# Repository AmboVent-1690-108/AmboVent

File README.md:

# AmboVent  1690.108

[![Travis Status][S]][T]

    Automatic, Controlled Resuscitator Device
    Emergency ventilation alternative system
    Global Partnership for the Greater good
    Leading Open Source Code Mentality Initiative

## Emergency ventilation initiative coming out of Israel

## The device was not tested yet for its performance or safety; it is NOT approved for clinical use

### Who is behind it?  
**Lead by the CTO & innovation leader of the Israeli Air-Force 108 Electronic Depot and backed by a large community of innovators behind him, to include:**

1. 40 Professional Volunteers
1. Magen David Adom (Israel’s national EMS)
1. Physicians from leading Israeli hospitals such as Tel Aviv Sourasky and Hadassah JLM as well as other medical centers, Engineers, FIRST Israel mentors and students
1. The Haifa Technological Center Rafael
1. Israel Aerospace Industries
1. IAF Unit 108
1. The garage program by Microsoft Israel
1. IDC Herzeliya
1. and others...

## Developer Chat on Gitter:

## [AmboVent Website](https://1nn0v8ter.rocks/AmboVent-1690-108)

## [BOM list](https://docs.google.com/spreadsheets/d/1yqxRhruZpR-hO4cpbX6UkSeXTlXk1JLd_4aYDwuWj4k/edit?usp=sharing)

# AmboVent's Standard Copyright and Disclaimer Notice:

*Copyright ©2020. THE AMBOVENT GROUP FROM ISRAEL herby declares:  No Rights Reserved. Anyone in the world have Permission to use, copy, modify, and distribute this software and its documentation for educational, research, for profit, business and not-for-profit purposes, without fee and without a signed licensing agreement, all is hereby granted, provided that the intention of the user is to use this code and documentation to save human lives  anywhere in the world. For any question, contact dreliram@gmail.com.*

***IN NO EVENT SHALL THE AMBOVENT GROUP FROM ISRAEL, BE LIABLE TO ANY PARTY FOR DIRECT, INDIRECT, SPECIAL, INCIDENTAL, OR CONSEQUENTIAL DAMAGES, INCLUDING LOST PROFITS, ARISING OUT OF THE USE OF THESE SPECS, LIST OF MATERIALS, ELECTRONIC DESIGNS , SOFTWARE CODE AND ANY DOCUMENTATION, EVEN IF THE AMBOVENT GROUP FROM ISRAEL HAS BEEN ADVISED OF THE POSSIBILITY OF SUCH DAMAGE.
THE AMBOVENT GROUP FROM ISRAEL DISCLAIMS ANY WARRANTIES, INCLUDING, BUT NOT LIMITED TO, THE IMPLIED WARRANTIES OF MERCHANTABILITY AND FITNESS FOR A PARTICULAR PURPOSE. THE SOFTWARE AND ACCOMPANYING DOCUMENTATION, SPECS, LIST OF MATERIALS, ELECTRONIC DESIGNS, SOFTWARE CODE AND ANY DOCUMENTATION IF PROVIDED HEREUNDER IS PROVIDED "AS IS". THE AMBOVENT GROUP FROM ISRAEL HAS NO CLAIM THAT IT IS COMPLETED OR FUNCTIONAL AND HAS NO OBLIGATION TO PROVIDE MAINTENANCE, SUPPORT, UPDATES, ENHANCEMENTS, OR MODIFICATIONS.***

# Setup

## Software

1. (Required to build the code): [Arduino IDE](https://www.arduino.cc/en/Main/Software)
1. (Optional: recommended to edit the code): Eclipse project for Arduino source code _editing_ (NOT building):
    1. A general setup PDF guide can be found in the [eRCaGuy_dotfiles](https://github.com/ElectricRCAircraftGuy/eRCaGuy_dotfiles) project [here](https://github.com/ElectricRCAircraftGuy/eRCaGuy_dotfiles/blob/master/eclipse/Eclipse%20setup%20instructions%20on%20a%20new%20Linux%20(or%20other%20OS)%20computer.pdf). See also:
    1. [3-Software/Arduino/readme.md](3-Software/Arduino/readme.md).
    1. [3-Software/Arduino/arduino_core/readme.md](3-Software/Arduino/arduino_core/readme.md)
    1. [3-Software/Arduino/.clang-format](3-Software/Arduino/.clang-format) - there are some nice descriptions & info in here on Eclipse & Sublime Text 3 editors, as well as setting your Arduino IDE to use 4 spaces instead of 2 for tabs.
1. (Required to get a pull request accepted which modifies the code): `clang-format` automatic code format tool. Please run this on any PR (GitHub Pull Request) before submitting a PR!
    1. Linux (tested--works): 
        1. Install: 

                # Install it:
                sudo apt update
                sudo apt install clang-format

                # Ensure you have version 6 (the default for Ubuntu 18), for compatibility with 
                # the .clang-format file we are using; sample output: 
                # `clang-format version 6.0.0-1ubuntu2 (tags/RELEASE_600/final)`
                clang-format --version
        
        1. Use it: 
            1. Commit your changes so everything is backed up.
            1. Then run the clang formatter:

                    ./run_clang-format.sh

            1. Then review and commit these changes, if any.
            1. Now do a Pull Request.

    1. Windows:
        1. Install:
            1. Download and install [Git for Windows](https://git-scm.com/download/win)
            1. Download and install LLVM (which includes `clang-format`) version **6.0.1** (for compatibility--see above) [for Windows, here](https://releases.llvm.org/download.html). Here's a [direct link](https://releases.llvm.org/6.0.1/LLVM-6.0.1-win64.exe) if you like for the 64-bit version.
        1. Use it:
            1. Using the git bash terminal that comes with git for Windows, run the script:

                    ./run_clang-format.sh

            1. Make sure to do this before making any Pull Request (see Linux "Use it" instructions just above as well).

# Software Changelog
- Newest on top
- Follows Semantic Versioning: MAJOR.MINOR.PATCH; see: https://semver.org/ for rules & FAQ.
- The 6 most common recommended types of changes are (see here: https://keepachangelog.com/en/1.0.0/): Added, Changed, Deprecated, Removed, Fixed, Security

INITIAL DEVELOPMENT PHASE:
- Use version numbers 0.MINOR.PATCH for the initial development phase; ex: 0.1.0, 0.2.0, etc.
- Increment just the MINOR version number for each new 0.y.z development phase enhancement, until the project is mature enough that you choose to move to a 1.0.0 release
- You may increment the PATCH number for bug fixes to your development code, or just increment the MINOR version number if there are also enhancements

MORE MATURE PHASE:
- As the project matures, release a 1.0.0 version
- Once you release a 1.0.0 version, do the following (copied from semver.org):
- Given a version number MAJOR.MINOR.PATCH, increment the:  
1. MAJOR version when you make incompatible API changes,  
2. MINOR version when you add functionality in a backwards compatible manner, and  
3. PATCH version when you make backwards compatible bug fixes.  

## [v0.1.0] - 2020-04-22
- Added: changelog and started tracking a software "version" number via the changelog
- Fixed: continued incremental improvements of the software formatting and style: ex: moved global variables to their own lines

[S]: https://travis-ci.org/labeneator/AmboVent.svg?branch=master
[T]: https://travis-ci.org/github/labeneator/AmboVent

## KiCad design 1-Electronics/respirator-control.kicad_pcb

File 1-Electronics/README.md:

AmboVent Electronic Design
--------------------------
## This directory contains the files needed to produce and/or change the electronic control board of AmboVent.

### The controller consist of a single PCB, with Arduino Nano mounted on it and a few other components. The board contains header connectors for varios system components:
- Front panel controls (pushbuttons, potentiometers, LEDs)
- Power input
- PWM control to the main motor
- Arm location feedback (potentiometer)
- I2C pressure sensor
 
All connectors have 0.1" spacing, and can accept either male or female headers. The power
input connector has 5mm spacing and it is designed for screw terminal connector type, but
direct wire connection is also feasible.

The PCB is designed with single layer, quick CNC fabrication in mind. It can be milled
with 1/32 mill. In this case, assembly will require a few wire bridges. If traditional, 
two layer fabrication method is used, a top layer can be used in place of the wire bridges.

#### SW1 – D2 - test button (used to initiate calibration)
#### SW2 – D4 - toggle breath on/off
#### SW3 – D5 - reset alarm button
#### Pot 1 – A2 – sets the range of motion as percentage from full range as set in calibration
#### Pot 2 – A3 – sets the respiration rate from 6 to 24 per minute
#### Pot 3 – A6 – sets the inspirium pressure from 30 to 70 cm H2O
#### J3 – connects to the position sensor potentiometer in the arm
#### J4 – connects to the motor controller PWM input (usually don’t connect the 5V)
#### J5 – connector to pressure sensor – if you use a 3.3V pressure sensor – supply 3.3V from the Arduino instead of the 5V

**Assemble the potentiometer for arm position sense such that when the arm moves down (presses the
Ambu more) – the voltage goes up. Range 0-5 volts
Assemble the user interface potentiometers such that during clockwise motion the voltage goes up.
Range 0-5 volts
Motor polarity shall be set such that PWM>50% to the controller results in the arm pressing the Ambu
(moving down).
The SW calibration procedure enable easy verification of the motor and position feedback polarity
(see calibration video for details)**

_Please note that the current sensor is **NOT** needed if you are using pressure sensor, it's possible to use it to monitor and limit the motor current while using the pressure sensor but again, not mandatory._

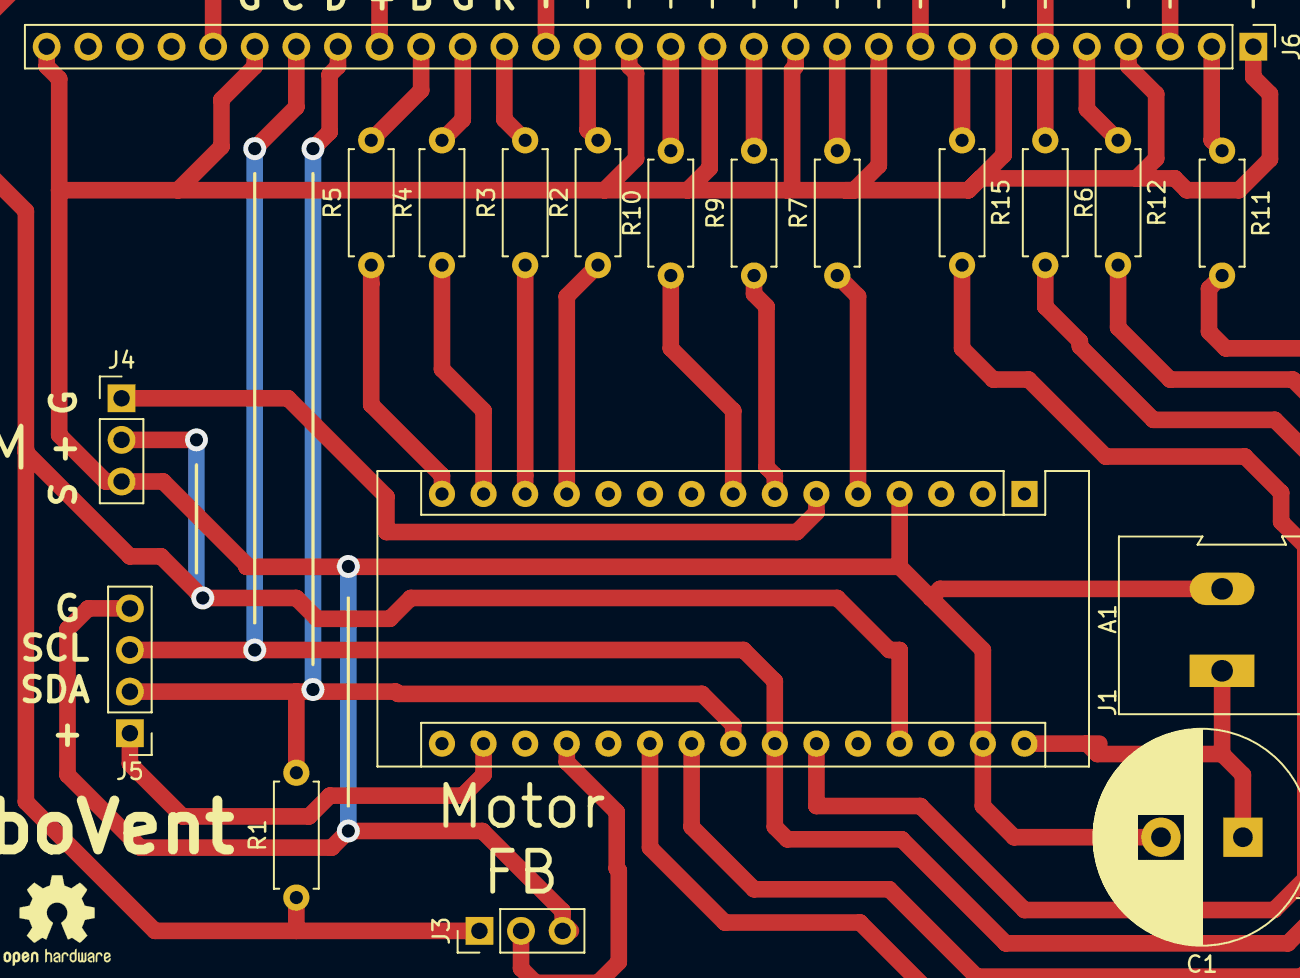
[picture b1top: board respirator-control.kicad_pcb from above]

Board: 2 copper layers, 23 parts (0 on the bottom side), 28 nets.

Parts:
A1: Arduino_Nano_v3.x; Arduino_Nano
C1: CP; CP_Radial_D13.0mm_P5.00mm
H1, H2, H3, H4: MountingHole; MountingHole_3.2mm_M3
J1: Conn_01x02; TerminalBlock_Altech_AK300-2_P5.00mm
J3, J4: Header 1X3; PinHeader_1x03_P2.54mm_Vertical
J5: Header 1X4; PinHeader_1x04_P2.54mm_Vertical
J6: Header 1X30; PinHeader_1x30_P2.54mm_Vertical
R1, R6: 4.7K; R_Axial_DIN0207_L6.3mm_D2.5mm_P7.62mm_Horizontal
R2, R3, R4, R5, R7, R9, R10, R11, R12, R15: 100; R_Axial_DIN0207_L6.3mm_D2.5mm_P7.62mm_Horizontal

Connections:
+3V3: A1.17, J5.1
+5V: A1.27, J3.1, J4.2, J6.3, J6.6, J6.9, J6.18, J6.22, J6.26, R1.1, R6.1
/CT1: J6.2, R11.1
/CT2: J6.5, R12.1
/CT3: J6.8, R15.1
/LED1: J6.17, R2.2
/LED2_B: J6.21, R5.2
/LED2_G: J6.20, R4.2
/LED2_R: J6.19, R3.2
/MOTOR_FB: A1.19, J3.2
/MOTOR_PWM: A1.6, J4.1
/SCL: A1.24, J5.3, J6.24, R6.2
/SDA: A1.23, J5.2, J6.23, R1.2
/SW1: J6.11, R7.2
/SW2: J6.13, R9.2
/SW3: J6.15, R10.2
GND: A1.4, A1.29, C1.2, J1.2, J3.3, J4.3, J5.4, J6.1, J6.4, J6.7, J6.10, J6.12, J6.14, J6.16, J6.25, J6.30
unnamed: A1.5, R7.1
unnamed: A1.7, R9.1
unnamed: A1.8, R10.1
unnamed: A1.12, R2.1
unnamed: A1.13, R3.1
unnamed: A1.14, R4.1
unnamed: A1.15, R5.1
unnamed: A1.21, R11.2
unnamed: A1.22, R12.2
unnamed: A1.25, R15.2
unnamed: A1.30, C1.1, J1.1

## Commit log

2020-03-31 Version 1 and first commit
2020-03-31 Giora's changes:
    Add disclaimer.
    Added Command and Control setup
    Added test button - still not in use
    Fix pres_pot range
    Moved clinical const up.
    Fix pin_USR LED for config 1.
2020-03-31 Moved code to it's folder so it could be open in arduino's IDE
2020-03-31 Some formatting
2020-03-31 Same
2020-04-01 Update
    Update
2020-04-01 v12 - added test texts
2020-04-01 param
2020-04-01 first commit - mechanisms design
2020-04-01 typo correction
2020-04-01 Create LICENSE
2020-04-02 added footage
2020-04-02 rename
2020-04-02 Documentation: Fix typo
    Fix typo in directory name 'Documentation'.
2020-04-02 added pot calibration and fail messages
2020-04-02 range from 33
2020-04-02 added filters to pot (for shoham :-) )
2020-04-02 fixed small disp bug
2020-04-02 minor bug in min_pres display
2020-04-02 added motor definition and comments to SW code
2020-04-02 Update BOM.url
    https://docs.google.com/spreadsheets/d/1yqxRhruZpR-hO4cpbX6UkSeXTlXk1JLd_4aYDwuWj4k/edit?usp=sharing
2020-04-02 Added BOM url and fixed site format
2020-04-02 Removed url files, organized folders
2020-04-02 Prioritized folders order
2020-04-03 Removed redundant parts
2020-04-03 Order in mechanism folder
2020-04-03 Upload the most updated schematic + PCB
2020-04-03 Add README file
2020-04-04 added clarification to Elec, updated Calib UI in SW
2020-04-04 minor update
2020-04-04 added calibration video
2020-04-04 Replaced electronic clariifcation docx with PDF file
2020-04-04 Added images and fixed names in pressure sensor folder
2020-04-04 fixed small bug in display
2020-04-04 fixed bud - sometime display was not updated @24 BPM
2020-04-04 fixed bug - sometime display was not updated @24 BPM
2020-04-04 updated disclaimer
2020-04-04 Moved presser sensor to its own folder and add some more files to it
2020-04-06 Added 3 pagers documentation in English, German Italian and Spanish
2020-04-06 Added Q-A to doc folder
2020-04-06 Added x_t parts files to mechanics
2020-04-06 Fixed line 502 #9
    #9
2020-04-06 added menu, changed SW structure to state machines
2020-04-06 added Arduino libs
2020-04-06 moved the calibration video to BU folder - not updated
2020-04-06 added more comments :-)
2020-04-07 Added drawings to mechanics
2020-04-07 Update credits
2020-04-08 add simple gitignore
2020-04-08 remove desktop.ini
2020-04-08 added pdf of Schematic file
2020-04-08 ventilation mahcine readability
2020-04-08 accepted readability improvements
2020-04-12 Rename folders to make them not hidden; add Linux URL to YouTube demo video; update readme
    Files and folders that begin with a period (.) on Linux and Mac are
    hidden, so I have renamed the following folders to make them not hidden
    anymore, while still keeping them near the top of the alphabetical
    order, which seemed to be intentional, and keeping them in the same
    order:
    1. .Electronics --> 1-Electronics
2020-04-12 updated code structure, added test, menu functions
2020-04-12 free a lot of RAM using PROGMEM
    thanks for the advice ElectricRCAircraftGuy
2020-04-12 Add Eclipse project to index and be able to explorer all Arduino source code
    This includes the AmboVent .ino file as well as ALL Arduino core source
    code as well!
2020-04-12 Do minor formatting changes to comments at top of ventilation_machine.ino
2020-04-12 Add custom Eclipse C/C++ formatter w/2 spaces for tabs, & braces on next line
2020-04-12 Add arduino_core folder & "3-Software/Arduino/arduino_core/readme.md" readme
2020-04-12 Add 3-Software/Arduino/arduino_core/readme.md & .gitignore file
2020-04-12 Now that the Eclipse project is set up, save ventilation_machine.ino in Eclipse to delete trailing white-space
2020-04-12 Save in Eclipse to delete trailing whitespace again now that I've rebased onto latest master
2020-04-12 Added an idea for an "African Solution" which is a simple solution which can be built using scrap parts which are integrated into a system to serve the purpose.
2020-04-12 added ascii art
2020-04-12 corrections
2020-04-13 #27 Fixed all warnings, warnings caused by implicit convert between strings to char*
2020-04-14 Add clang-format files, including .clang-format rules file & run_clang-format.sh scripts
2020-04-14 wip: update main readme
2020-04-14 Add ventilation_machine/readme.md to log build size info; move `#include`s to top of .ino file
    ...and alphabetize them
2020-04-14 Fix .clang-format file since I accidentally set it according to version 11 of clang-format but I only have version 6
    Version 6 Style Options documentation is here:
    https://releases.llvm.org/6.0.1/tools/clang/docs/ClangFormatStyleOptions.html
    I had to comment out or modify every line that was giving a clang-format
    error when running clang-format. These lines I commented out or changed
    are apparently only for version 11, but I have version 6.
2020-04-14 Update .clang-format doc with desired settings
    I set every single setting, meticulously going through this
    documentation online to do so:
    https://clang.llvm.org/docs/ClangFormatStyleOptions.html
2020-04-14 Fix .clang-format file
    1. AlwaysBreakAfterReturnType - change from "All" to "None", as All was
    an accident and makes functions look like this:
    void
    main()
    {
    }
2020-04-14 .clang-format: changed tab size from 2 --> 4 & added detailed info about getting a good editor
    I explained how to set tab size in Arduino IDE from 2 to 4, but also
    recommended just getting a good editor, and setting the IDE to "Use
    external editor", so you just build with it, but no longer edit with it.
    Good editor examples & descriptions
    (I added detailed descriptions for these editors):
    1. Eclipse
2020-04-14 Update the main README to document clang-format installation & usage
2020-04-14 Run `./run_clang-format.sh` to fix all formatting in ventilation_machine.ino
2020-04-14 ignore .DS_Store files from osx
2020-04-14 Update main README Windows installation instructions for clang-format
    Now that @nimrod46 has tested the instructions and says they work, I can
    remove the part saying the instructions were untested and I needed help
    to test them.
2020-04-14 initial travis ci integration
2020-04-14 bugfix. remove errant line from source of ci file
2020-04-14 travis ci badge
2020-04-14 bugfix readme travis badge
2020-04-14 Conditionalize central monitoring code in the preprocessor
    Because ArduinoUniqueID gives a compile error on megaAVR archs
2020-04-14 Fully qualify arduino::Print
    To avoid compile error on megaAVR boards (may not be backwards compatible to other boards)
2020-04-15 Conditionalize arduino::Print on arch
2020-04-16 add library
2020-04-16 renames variable
2020-04-16 magnetic position encoder
2020-04-17 Added flow sensor library
2020-04-17 Replaced byte with uint8_t in the arduino files.
2020-04-18 Fixed compression change effect during respiration
    Only before every respiration, the compression value will take effect.
    This will prevent unwanted behavior when the user change the compression during respiration.
    Code was tested on the ambovent.
    Runned clang format.
2020-04-19 Added sensor flow and the calculation of volumetric flow rate in liter per minutes
    Not tested
2020-04-20 Add ".github/pull_request_template.md" PR template
    Resolves #44
2020-04-20 Add clarity & comments to the PR request template
2020-04-20 Added Bluetooth basic support, bluetooth does not know state of connection (we need another pin for state (connected)) we cannot use Serial when bluetooth is needed, pins 0,1 must be clear of wires i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
2020-04-21 I opened the Eclipse project on a new computer which caused a hash change in "3-Software/Arduino/.settings/language.settings.xml"
    If this becomes problematic, causing a hash change for anyone who opens
    this file in Eclipse, we'll have to add this file to the .gitignore
    list. Sharing Eclipse configuration files in version control is still
    a bit new to me.
2020-04-21 ./run_clang-format.sh
2020-04-21 Clean up the top section of #defines; change all `byte` types to `uint8_t`
    Cleaning up the #defines included:
    1. renaming to have more descriptive names, names in ALL_CAPITALS, and
    names which ended in their units (ex: _PA for Pascals)
    2. Changing all 0s meaning false to `false`, all 1s meaning true to
    `true`
    3. Adding more detailed descriptions, such as for the low-pass-filter
2020-04-21 Update ventilation_machine/readme.md to show it still builds in Arduino w/virtually no binary size changes
2020-04-21 .github/pull_request_template.md: add a comment
    I added a comment to explain what markdown comments are, and that they
    don't have to be deleted, yet they won't show up in markdown text.
2020-04-21 This is just a test PR to see how the PR template on github looks now
2020-04-21 Update ".github/pull_request_template.md" with correct readme URL & other minor fixes
2020-04-21 Main readme.md: do some minor additions in the Software section
2020-04-21 Added drawings to specific parts
2020-04-21 Fixed flow consts to much format and added back "SoftwareSerial.h"
2020-04-22 Do a ton more incremental improvements to the software formatting
    - Change #define section from two #ifs to #if #else
    - moved global variables to one per line
    - changed some types to use stdint.h types
    - added a few comments and some doxygen
    Also:
    - added a changelog
2020-04-22 Update more variables to use stdint.h types; add todos
2020-04-22 Simplify the GitHub pull_request_template.md doc a bit
2020-04-22 fix for BLE_enabled breaking compilation if 0
2020-04-26 Calibrated ambovent PID
2020-04-26 Fixed sensor lib and calculation
2020-04-28 Added RGB led, moved motion_failure check to calc_failure func
    Runned code formatting with "./run_clang-format.sh"
2020-04-28 WIP, started flow close loop
2020-04-28 Added the correct SDP sensor lib
2020-04-28 Finished writing the close loop flow, WPI not tested
2020-04-29 WIP - fixed some logic in loop
2020-05-01 Turned off by default
2020-05-01 Fixed Clang YAML
2020-05-05 Changed BLE pins to 7-8 and updated BLE response to json structure sent every 20 ms, still some values are missing.
2020-05-06 Update the GitHub pull request template to be clearer
    ...and cause less confusion about what is being asked for.
2020-05-08 Add "Developer Chat on Gitter" link to readme
